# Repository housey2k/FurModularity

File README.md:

# FurModularity
Smart watch/audio mixer/module hub/game console/whatever
The FurModularity is a """watch""" meant "For Modularity", it's based on a ESP32-S3 as it's brain

It has 5 input/output connectors for external modules, these modules can be anything, be it a flashlight, a laser pointer, SD card, a second screen, or anything you can imagine, these modules interface with the main board through a SPI bus, a microcontroller inside the module card must interface between the actual module device and the ESP32, this allows more flexibility since a driver on the watch and custom code on the slave microcontroller allows for way more customization than directly interfacing the SPI bus with the module device, it would result in a way more limited module selection, or require you to manually select what kind of module is connected on the user inteface, which would ruin the hotplugging since you'd need to open settings every time you connect something new.

It also has a two input and two output audio mixer, via software you can route inputs 1, 2 or both to outputs 1, 2 or both, the routing is done by two 74VHC4066M Analog Switch ICs, one for each input channel, and you can also change the input volumes, that is done by two MCP4261 ICs, one for each channel too.

I originally built this project as a curious kid exploring CAD software, and I always liked electronics, I wanted to create my own stuff, but I never had the money for it. Now with more experience I restarted this project from scratch hoping to get funds for it.

This is how the PCB looks like, the back side has no components, thus simplifying assembly:

This is how the case looks like:

And finally, here is the schematics:
This is the power circuit, it handles battery discharging, PowerPath, and generating 5V and 3.3V rails

This is the digital circuit, it shows connections from the MCU to other components in the board

This is the audio circuit, it handles audio routing and volume control, everything is controlled by the MCU

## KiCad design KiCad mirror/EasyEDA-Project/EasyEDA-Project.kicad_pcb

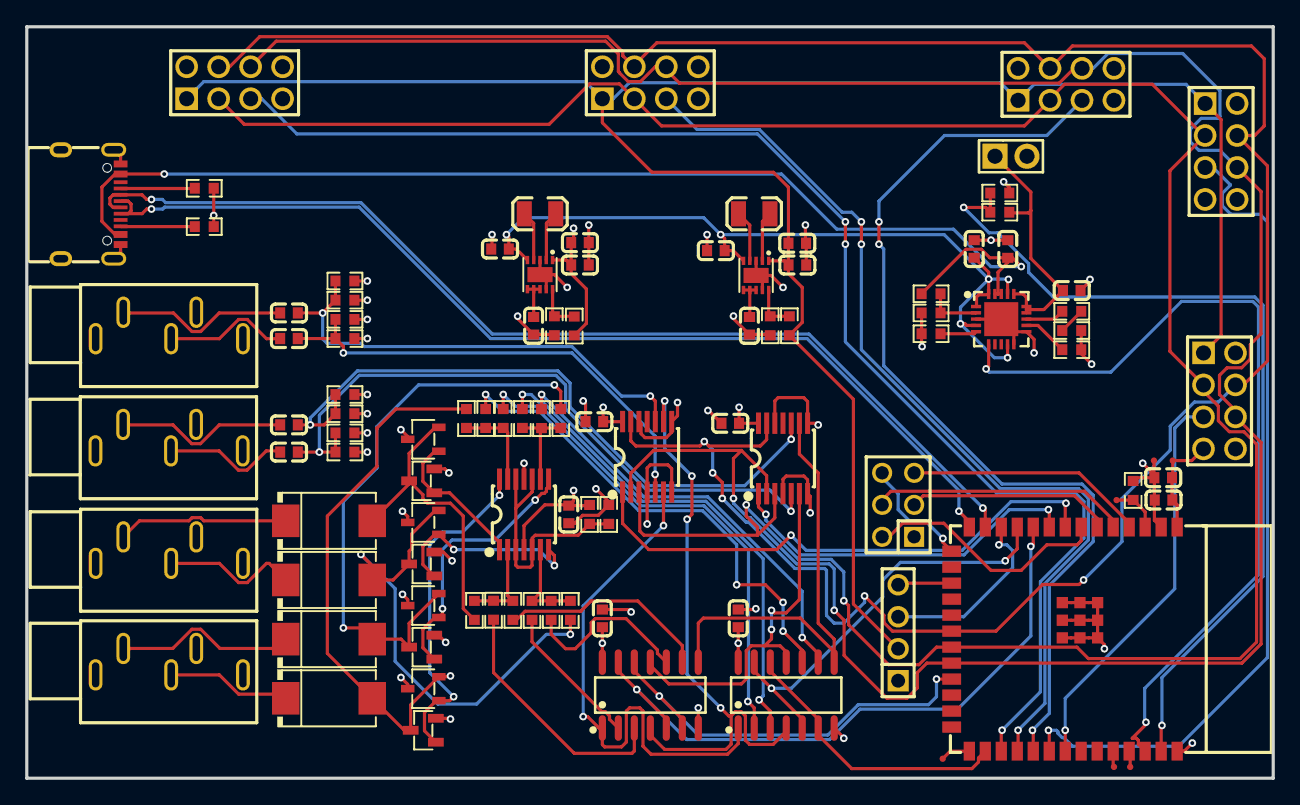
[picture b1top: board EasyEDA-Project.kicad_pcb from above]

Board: 4 copper layers, 99.0 x 59.7 mm, 101 parts (0 on the bottom side), 87 nets.

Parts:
C1, C2, C3, C4, C5, C6, C7, C8, C9, C10, C11, C12, C13, C43, C44, C45, C46, C47, C54, C55, C56, C57: C0603
C48, C49, C50, C51: CAP-SMD_L7.3-W4.3-FD
CN5, CN6, CN7, CN8: AUDIO-TH_KH-PJ-325C
H1: HDR-TH_2P-P2.54-V-M
H2: HDR-TH_4P-P2.54-V-M
H3: HDR-TH_6P-P2.54-V-R2-C3-S2.54_A2541WV-2X3P
H4, H5, H6, H7, H8: HDR-TH_8P-P2.54-V-R2-C4-S2.54_A2541WV-2X4P
L1, L2: L1207
Q1, Q3, Q5, Q7: SOT-23-3_L2.9-W1.6-P1.90-LS2.8-BR
Q2, Q4, Q6, Q8: SOT-23-3_L2.9-W1.3-P1.90-LS2.4-BR
R1, R2, R3, R4, R5, R7, R8, R9, R10, R11, R12, R14, R15, R23, R24, R25, R26, R27, R28, R29, R30, R31, R32, R33, R34, R39, R40, R41, R42, R43, R44, R45, R46, R49, R50, R51, R52: R0603
TP1, TP2, TP3, TP4, TP5, TP6: Test-Point-0.5mm
U1: QFN-20_L4.0-W4.0-P0.50-BL-EP2.7
U2, U3: SON-10_L2.5-W2.5-P0.50-TL-EP
U4: WIFIM-SMD_ESP32-S3-WROOM-1-N8
U6, U7, U8: TSSOP-14_L5.0-W4.4-P0.65-LS6.4-BL
U10, U12: SOIC-14_L8.7-W3.9-P1.27-LS6.0-BL
USB1: USB-C-SMD_TYPE-C-6PIN-2MD-073

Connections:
3V3: C6.1, C7.1, C12.1, C13.1, C43.2, C44.2, C45.2, C46.1, C47.1, H4.8, H5.8, H6.8, H7.8, H8.8, Q1.3, Q3.3, Q5.3, Q7.3, R8.2, R12.2, R39.2, R41.2, R43.2, R45.2, R51.2, TP5.1, U2.1, U4.2, U6.14, U7.14, U8.4, U10.14, U12.14
5V: C10.1, C11.1, H2.2, H4.1, H5.1, H6.1, H7.1, H8.1, R10.2, U3.1
$1N480: R1.2, USB1.4
$1N506: R2.2, USB1.10
$1N1632: R3.1, R4.2, U1.2
$1N1764: R5.2, U1.5
$1N1839: R15.2, U1.13
$1N1881: R7.2, U1.12
$1N2370: C5.1, U2.6, U2.7, U2.8
$1N2432: L1.2, U2.2
$1N2438: L1.1, U2.4
$1N2461: R8.1, R9.2, U2.10
$1N3033: R10.1, R11.2, U3.10
$1N3038: L2.2, U3.2
$1N3051: C9.1, U3.6, U3.7, U3.8
$1N3063: L2.1, U3.4
$1N4175: R14.2, R15.1
$2N491: TP2.1, U4.27
$2N495: R12.1, TP1.1, U4.3
$2N518: TP3.1, U4.37
$2N539: TP4.1, U4.36
$3N1138: R23.1, R33.2, R34.2, U8.2
$3N1139: R24.1, R25.2, R26.2, U8.6
$3N1144: R27.2, R28.2, R29.1, U8.13
$3N1145: R30.1, R31.2, R32.2, U8.9
$3N1256: Q5.1, Q6.1, U8.8
$3N2308: Q1.1, Q2.1, U8.1
$3N2351: Q3.1, Q4.1, U8.7
$3N2603: Q7.1, Q8.1, U8.14
CLK: H4.6, H5.6, H6.6, H7.6, H8.6, U4.22, U6.2, U7.2
CS1: H4.5, U4.29
CS2: H5.5, U4.30
CS3: H6.5, U4.31
CS4: H7.5, U4.32
CS5: H8.5, U4.33
CTRL_IN1_OUT1: U4.10, U10.5, U10.13
CTRL_IN1_OUT2: U4.11, U12.5, U12.13
CTRL_IN2_OUT1: U4.23, U10.6, U10.12
CTRL_IN2_OUT2: U4.28, U12.6, U12.12
DOWN: H3.4, U4.5
ENTER: H3.6, U4.15
GND: C1.1, C2.2, C3.2, C4.2, C5.2, C6.2, C7.2, C8.2, C9.2, C10.2, C11.2, C12.2, C13.2, C43.1, C44.1, C45.1, C46.2, C47.2, CN5.1, CN6.1, CN7.1, CN8.1, H1.2, H2.1, H3.1, H4.2, H4.7, H5.2, H5.7, H6.2, H6.7, H7.2, H7.7, H8.2, H8.7, Q2.2, Q4.2, Q6.2, Q8.2, R1.1, R2.1, R4.1, R5.1, R7.1, R9.1, R11.1, R14.1, R40.1, R42.1, R44.1, R46.1, R50.1, R52.1, TP6.1, U1.3, U1.10, U1.11, U1.21, U2.3, U2.9, U2.11, U3.3, U3.9, U3.11, U4.1, U4.40, U4.41, U6.4, U6.7, U6.8, U6.12, U7.4, U7.7, U7.8, U7.12, U8.11, U10.7, U12.7, USB1.1, USB1.12, USB1.13, USB1.14
IJACK1_L: C55.2, CN5.5
IJACK1_R: C54.2, CN5.2
IJACK2_L: C57.2, CN6.5
IJACK2_R: C56.2, CN6.2
IN1_L: C55.1, R41.1, R42.2, U6.10
IN1_L_SW1: R33.1, U10.3
IN1_L_SW2: R32.1, U12.3
IN1_POTOUT_L: U6.9, U10.4, U12.4
IN1_POTOUT_R: U6.6, U10.1, U12.1
IN1_R: C54.1, R39.1, R40.2, U6.5
IN1_R_SW1: R25.1, U10.2
IN1_R_SW2: R28.1, U12.2
IN2_L: C57.1, R45.1, R46.2, U7.10
IN2_L_SW1: R34.1, U10.9
IN2_L_SW2: R31.1, U12.9
IN2_POTOUT_L: U7.9, U10.8, U12.8
IN2_POTOUT_R: U7.6, U10.11, U12.11
IN2_R: C56.1, R43.1, R44.2, U7.5
IN2_R_SW1: R26.1, U10.10
IN2_R_SW2: R27.1, U12.10
LEFT: H3.2, U4.7
MISO: H4.4, H5.4, H6.4, H7.4, H8.4, U4.20, U6.13, U7.13
MOSI: H4.3, H5.3, H6.3, H7.3, H8.3, U4.21, U6.3, U7.3
OJACK1_L: C48.1, CN7.5
OJACK1_R: C49.1, CN7.2
OJACK2_L: C51.1, CN8.5
OJACK2_R: C50.1, CN8.2
OUT1_L: C48.2, Q1.2, Q2.3, R23.2
OUT1_R: C49.2, Q3.2, Q4.3, R24.2
OUT2_L: C51.2, Q5.2, Q6.3, R30.2
OUT2_R: C50.2, Q7.2, Q8.3, R29.2
P1_CS: U4.8, U6.1
P2_CS: U4.9, U7.1
REF_1V65: R51.1, R52.2, U8.3, U8.5, U8.10, U8.12
RIGHT: H3.3, U4.6
SCL: H2.4, U4.17
SDA: H2.3, U4.12
UP: H3.5, U4.4
USB_DM: U4.13, USB1.5, USB1.7
USB_DP: U4.14, USB1.6, USB1.8
USB_SENSE: U1.6, U4.38
VBAT: C3.1, H1.1, R49.2, U1.14, U1.15, U1.16
VBAT_SENSE: R49.1, R50.2, U4.39
VBUS: C1.2, R3.2, U1.18, U1.19, USB1.2, USB1.11
VSYS: C2.1, C4.1, C8.1, U1.1, U1.4, U1.9, U1.17, U1.20, U2.5, U3.5

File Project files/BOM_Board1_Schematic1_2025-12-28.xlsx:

No. | Quantity | Comment | Designator | Footprint | Value | Manufacturer Part | Manufacturer | Supplier Part | Supplier | LCSC Price | LCSC Stock | JLCPCB Price | Pin Count | Primary Category | Secondary Category | JLCPCB Stock
1 | 13 | 10uF | C1,C4,C6,C7,C8,C10,C11,C46,C47,C54,C55,C56,C57 | C0603 | 10uF | C0603B106M007T | IHHEC(禾伸堂) | C7094065 | LCSC |  |  | 0.0012 | 2 |  |  | 3674
2 | 2 | 4.7uF | C2,C3 | C0603 | 4.7uF | CL10A475KP8NNNC | SAMSUNG(三星) | C1705 | LCSC |  |  | 0.0008 | 2 |  |  | 3827044
3 | 7 | 100nF | C5,C9,C12,C13,C43,C44,C45 | C0603 | 100nF | CC0603KRX7R9BB104 | YAGEO(国巨) | C14663 | LCSC |  |  | 0.0004 | 2 |  |  | 68279201
4 | 4 | 470uF | C48,C49,C50,C51 | CAP-SMD_L7.3-W4.3-FD | 470uF | CA45-D-6.3V-470UF-K | CEC(振华新云) | C2841148 | LCSC |  |  | 0.1055 | 2 |  |  | 371
5 | 4 | KH-PJ-325C | CN5,CN6,CN7,CN8 | AUDIO-TH_KH-PJ-325C |  | KH-PJ-325C | kinghelm(金航标) | C5123138 | LCSC |  |  | 0.0263 | 5 | Connectors | Audio Connectors | 425
6 | 1 | PZ254V-11-02P | H1 | HDR-TH_2P-P2.54-V-M |  | PZ254V-11-02P | XFCN(兴飞) | C492401 | LCSC |  |  | 0.0018 | 2 | Connectors | Pin Headers | 576750
7 | 1 | PZ254V-11-04P | H2 | HDR-TH_4P-P2.54-V-M |  | PZ254V-11-04P | XFCN(兴飞) | C2691448 | LCSC |  |  | 0.0031 | 4 | Connectors | Pin Headers | 594475
8 | 1 | 2.54-2*3 | H3 | HDR-TH_6P-P2.54-V-R2-C3-S2.54_A2541WV-2X3P |  | 2.54-2*3 | ZHOURI(洲日) | C5116479 | LCSC |  |  | 0.0081 | 6 |  |  | 16497
9 | 5 | A2541WV-2x4P | H4,H5,H6,H7,H8 | HDR-TH_8P-P2.54-V-R2-C4-S2.54_A2541WV-2X4P |  | A2541WV-2x4P | CJT(长江连接器) | C225519 | LCSC |  |  | 0.0179 | 8 | Connectors | Pin Headers | 9182
10 | 2 | 1.5uH | L1,L2 | L1207 | 1.5uH | LB3218T1R5M | TAIYO YUDEN(太诱) | C223380 | LCSC |  |  | 0.0065 | 2 |  |  | 0
11 | 4 | MMBT2222A | Q1,Q3,Q5,Q7 | SOT-23-3_L2.9-W1.6-P1.90-LS2.8-BR |  | MMBT2222A | TDSEMIC(拓电半导体) | C42441802 | LCSC |  |  |  | 3 | Transistors/Thyristors | Bipolar (BJT) | 0
12 | 4 | MMBT2907A | Q2,Q4,Q6,Q8 | SOT-23-3_L2.9-W1.3-P1.90-LS2.4-BR |  | MMBT2907A | R+O(宏嘉诚) | C7420352 | LCSC |  |  | 0.002 | 3 | Transistors/Thyristors | Bipolar (BJT) | 65573
13 | 2 | 5.1kΩ | R1,R2 | R0603 | 5.1kΩ | HoAR0603-1/10W-5.1KR-0.1%-TCR25 | Milliohm(毫欧) | C5123587 | LCSC |  |  | 0.0072 | 2 |  |  | 974
14 | 1 | 330kΩ | R3 | R0603 | 330kΩ | HPCR0603F330KK9 | RESI(开步睿思) | C365145 | LCSC |  |  | 0.0001 | 2 |  |  | 0
15 | 1 | 110kΩ | R4 | R0603 | 110kΩ | PTFR0603B110KN9 | RESI(开步睿思) | C2692888 | LCSC |  |  | 0.0255 | 2 |  |  | 3518
16 | 10 | 10kΩ | R5,R12,R39,R40,R41,R42,R43,R44,R45,R46 | R0603 | 10kΩ | SCR0603J10K | VO(翔胜) | C3017715 | LCSC |  |  | 0.0002 | 2 |  |  | 104777
17 | 1 | 100kΩ | R7 | R0603 | 100kΩ | SCR0603F100K | VO(翔胜) | C3016388 | LCSC |  |  | 0.0002 | 2 |  |  | 13910
18 | 1 | 1.13MΩ | R8 | R0603 | 1.13MΩ | RTT031134FTP | RALEC(旺诠) | C166907 | LCSC |  |  | 0.0003 | 2 |  |  | 2966
19 | 2 | 200kΩ | R9,R11 | R0603 | 200kΩ | SCR0603F200K | VO(翔胜) | C5140262 | LCSC |  |  | 0.0002 | 2 |  |  | 14305
20 | 1 | 1.8MΩ | R10 | R0603 | 1.8MΩ | FRC0603J185TS | FOJAN(富捷) | C2930026 | LCSC |  |  | 0.0002 | 2 |  |  | 52884
21 | 18 | 1kΩ | R14,R15,R23,R24,R25,R26,R27,R28,R29,R30,R31,R32,R33,R34,R49,R50,R51,R52 | R0603 | 1kΩ | 0603WAF1001T5E | UNI-ROYAL(厚声) | C21190 | LCSC |  |  | 0.0002 | 2 |  |  | 46024417
22 | 6 | Test-Point | TP1,TP2,TP3,TP4,TP5,TP6 | Test-Point-0.5mm |  |  |  |  |  | 26.0869 |  |  | 1
23 | 1 | MCP73871-2CAI/ML | U1 | QFN-20_L4.0-W4.0-P0.50-BL-EP2.7 |  | MCP73871-2CAI/ML | MICROCHIP(美国微芯) | C185603 | LCSC |  |  | 0.575 | 21 | Power Management (PMIC) | Battery Management | 91
24 | 2 | TPS63030DSKTG4 | U2,U3 | SON-10_L2.5-W2.5-P0.50-TL-EP |  | TPS63030DSKTG4 | TI(德州仪器) | C2072808 | LCSC |  |  | 0.2416 | 11 | Power Management (PMIC) | DC-DC Converters | 0
25 | 1 | ESP32-S3-WROOM-1-N4 | U4 | WIFIM-SMD_ESP32-S3-WROOM-1-N8 |  | ESP32-S3-WROOM-1-N4 | ESPRESSIF(乐鑫) | C2913197 | LCSC |  |  | 0.6165 | 41 | IoT/Communication Modules | WiFi Modules | 1248
26 | 2 | MCP4261-103E/ST | U6,U7 | TSSOP-14_L5.0-W4.4-P0.65-LS6.4-BL |  | MCP4261-103E/ST | MICROCHIP(美国微芯) | C185580 | LCSC |  |  | 0.2885 | 14 |  |  | 0
27 | 1 | LMV324IPWRE4 | U8 | TSSOP-14_L5.0-W4.4-P0.65-LS6.4-BL |  | LMV324IPWRE4 | TI(德州仪器) | C4366614 | LCSC |  |  | 0.0426 | 14 |  |  | 0
28 | 2 | 74VHC4066M | U10,U12 | SOIC-14_L8.7-W3.9-P1.27-LS6.0-BL |  | 74VHC4066M | onsemi(安森美) | C3656918 | LCSC |  |  | 0.0364 | 14 |  |  | 0
29 | 1 | TYPE-C 16PIN 2MD(073) | USB1 | USB-C-SMD_TYPE-C-6PIN-2MD-073 |  | TYPE-C 16PIN 2MD(073) | SHOU HAN(首韩) | C2765186 | LCSC |  |  | 0.0089 | 14 | Connectors | USB Connectors | 347871

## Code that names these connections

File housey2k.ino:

#include <Wire.h>
#include <SPI.h>
#include <String.h>
#include <LiquidCrystal_I2C.h>
#include <MCP4261.h>

// SPI Bus BEGIN
#define MOD_CS1 36
#define MOD_CS2 37
#define MOD_CS3 38
#define MOD_CS4 39
#define MOD_CS5 40

#define P1_CS 15
#define P2_CS 16
// SPI Bus END

// GPIO BEGIN
#define ENTER 3
#define UP 4
#define DOWN 5
#define RIGHT 6
#define LEFT 7

#define CTRL_IN1_OUT1 17
#define CTRL_IN1_OUT2 18
#define CTRL_IN2_OUT1 21
#define CTRL_IN2_OUT2 35
// GPIO END

// BUS BEGIN
#define LCD_ADDR 0x27
#define SDA 8
#define SCL 9

#define MISO 12
#define MOSI 13
#define SCK 14
// BUS END

LiquidCrystal_I2C lcd(LCD_ADDR, 20, 4);
MCP4261 pot1(P1_CS, 255, &SPI);
MCP4261 pot2(P2_CS, 255, &SPI);

void I2C_Scan(void)
{
  byte error, address;
  int nDevices;

  Serial.println("Scanning...");
  nDevices = 0;
  for(address = 1; address < 127; address++ ) {
    Wire.beginTransmission(address);
    error = Wire.endTransmission();
    if (error == 0) {
      Serial.print("I2C device found at address 0x");
      if (address<16) {
        Serial.print("0");
      }
      Serial.println(address, HEX);
      nDevices++;
    }
    else if (error==4) {
      Serial.print("Unknow error at address 0x");
      if (address<16) {
        Serial.print("0");
      }
      Serial.println(address, HEX);
    }    
  }
  if (nDevices == 0) {
    Serial.println("No I2C devices found\n");
  }
  else {
    Serial.println("done\n");
  }
}

void spiSendBuffer(const uint8_t *buf, size_t len) {
  for (size_t i = 0; i < len; i++) {
    SPI.transfer(buf[i]);
  }
}

void spiReadBuffer(uint8_t *buf, size_t len) {
  for (size_t i = 0; i < len; i++) {
    buf[i] = SPI.transfer(0x00);
  }
}

String Module_scan() {
  static const uint8_t detectCmd[] = { 'D','E','T','E','C','T' };
  uint8_t reply[4];

  const uint8_t csList[] = {
    MOD_CS1,
    MOD_CS2,
    MOD_CS3,
    MOD_CS4,
    MOD_CS5
  };

  String output;
  output.reserve(sizeof(csList));

  SPI.beginTransaction(SPISettings(
    500000,
    MSBFIRST,
    SPI_MODE0
  ));

  for (size_t i = 0; i < sizeof(csList); i++) {
    digitalWrite(csList[i], LOW);
    delayMicroseconds(5);

    spiSendBuffer(detectCmd, sizeof(detectCmd));
    delayMicroseconds(20);          // give slave time
    spiReadBuffer(reply, sizeof(reply));

    digitalWrite(csList[i], HIGH);

    output += (memcmp(reply, "HERE", 4) == 0) ? '1' : '0';
    delay(5);
  }

  SPI.endTransaction();
  return output;
}

void print(String msg, bool printToLCD_Y3) {
  Serial.println(msg);
  if (!printToLCD_Y3) { return; }
  lcd.setCursor(0, 3);
  lcd.print("                    ");
  lcd.setCursor(0, 3);
  lcd.print(msg);
}

bool RW_MCP4261(MCP4261 pot, int wiper) {
  bool success = false;
  pot.setValue(wiper, 123);
  if (pot.getValueDevice(wiper) == 123) {
    success = true;
  }
  return success;
}

void halt() {
  while (true) {}
}

String Connected_modules;

bool RenderedMenu;
bool RenderedArrow;

int ArrowX;
int ArrowY;
int PrevArrowX;
int PrevArrowY;

String CurrMenu;

bool UpPressed;
bool DownPressed;
bool RightPressed;
bool LeftPressed;

int ArrowRawX;
int ArrowRawY;

void setup(void) {
  Serial.begin(115200);
  print("HouseY2K OS", false);

  Wire.begin(SDA, SCL);
  print("Initialized I2C bus", false);

  I2C_Scan();
  print("Hardcoded LCD addr: #define LCD_ADDR ", false);
  Serial.println(LCD_ADDR);

  lcd.init();
  print("LCD init() done", true);
  lcd.backlight();
  print("LCD backlight() done", true);

  lcd.print("FurModularity DEV FW");
  lcd.setCursor(0, 1);
  lcd.print("HouseY2K OS V0.1");
  lcd.setCursor(0, 2);
  lcd.print("Booting...");
  print("Initializing SPI...", true);
  SPI.begin(SCK, MISO, MOSI, -1);
  delay(100);

  print("Initializing pins...", true);
  pinMode(MOD_CS1, OUTPUT);
  pinMode(MOD_CS2, OUTPUT);
  pinMode(MOD_CS3, OUTPUT);
  pinMode(MOD_CS4, OUTPUT);
  pinMode(MOD_CS5, OUTPUT);

  pinMode(ENTER, INPUT_PULLUP);
  pinMode(UP, INPUT_PULLUP);
  pinMode(DOWN, INPUT_PULLUP);
  pinMode(RIGHT, INPUT_PULLUP);
  pinMode(LEFT, INPUT_PULLUP);

  pinMode(CTRL_IN1_OUT1, INPUT_PULLUP);
  pinMode(CTRL_IN1_OUT2, INPUT_PULLUP);
  pinMode(CTRL_IN2_OUT1, INPUT_PULLUP);
  pinMode(CTRL_IN2_OUT2, INPUT_PULLUP);

  delay(100);

  print("POST MCP4261", true);
  delay(100);

  print("INIT MCP4261", true);
  pot1.begin();
  pot2.begin();
  delay(100);

  print("RW MCP4261 IC1 W0", true);
  if (RW_MCP4261(pot1, 0)) {
    print("OK", true);
  } else {
    print("ERROR IC1 W0", true);
    halt();
  }

  delay(100);

  print("RW MCP4261 IC1 W1", true);
  if (RW_MCP4261(pot1, 1)) {
    print("OK", true);
  } else {
    print("ERROR IC1 W1", true);
    halt();
  }

  delay(100);

  print("RW MCP4261 IC2 W0", true);
  if (RW_MCP4261(pot2, 0)) {
    print("OK", true);
  } else {
    print("ERROR IC2 W0", true);
    halt();
  }

  delay(100);

  print("RW MCP4261 IC2 W1", true);
  if (RW_MCP4261(pot2, 1)) {
    print("OK", true);
  } else {
    print("ERROR IC2 W1", true);
    halt();
  }

  delay(100);
  

  print("Scanning modules...", true);
  Connected_modules = Module_scan();

  print("mdet:" + Connected_modules, true);

  delay(1000);
  print("Initializing vars", true);

  RenderedMenu = false;
  CurrMenu = "NULL";

  RenderedArrow = false;
  ArrowX = 0;
  ArrowY = 0;

  PrevArrowX = 0;
  PrevArrowY = 0;

  ArrowRawX = 0;
  ArrowRawY = 0;

  UpPressed = false;
  DownPressed = false;
  RightPressed = false;
  UpPressed = false;
  delay(100);
  print("BootOK LoadOS", true);
}


void RenderMainMenu(String Mods) {
  lcd.clear();
  lcd.setCursor(0, 0);

  lcd.print(" MODS USB ");
  lcd.setCursor(0, 1);
  lcd.print("MIXER PWR");
  lcd.setCursor(0, 2);
  lcd.print(" WiFi BATT");
  lcd.setCursor(0, 2);
  lcd.print(" BLE ");
}

void RenderArrow(int X, int Y) {
  RenderedArrow = true;
  lcd.setCursor(PrevArrowX, PrevArrowY);
  lcd.print(" ");
  lcd.setCursor(X, Y);
  lcd.print(">");
  PrevArrowX = X;
  PrevArrowY = Y;
}

// Gets the position to write the arrow on screen, rawpos is the numerical value based on the increments or decrements from left/right buttons
int GetArrowXPos(int rawPos) {
  if (CurrMenu == "MAIN") {
    if (rawPos == 0) {
      return 0;
    } else if (rawPos == 1) {
      return 5;
    } else if (rawPos == 2) {
      return 9;
    }
  }
  return 0;
}

// Gets the position to write the arrow on screen, rawpos is the numerical value based on the increments or decrements from up/down buttons
int GetArrowYPos(int rawPos) {
  /*if (CurrMenu == "MAIN") {
    if (rawPos == 0) {
      return 0;
    } else if (rawPos == 1) {
      return 1;
    } else if (rawPos == 2) {
      return 2;
    }
  }*/
  return rawPos;
}

void loop(void) {

  if (!digitalRead(UP) && !UpPressed) {
    UpPressed = true;
    RenderedArrow = false;
    ArrowRawY++;
  } else if (digitalRead(UP)) {
    UpPressed = false;
  }

  if (!digitalRead(DOWN) && !DownPressed) {
    DownPressed = true;
    RenderedArrow = false;
    ArrowRawY--;
  } else if (digitalRead(DOWN)) {
    DownPressed = false;
  }

  if (!digitalRead(RIGHT) && !RightPressed) {
    RightPressed = true;
    RenderedArrow = false;
    ArrowRawX++;
  } else if (digitalRead(RIGHT)) {
    RightPressed = false;
  }

  if (!digitalRead(LEFT) && !LeftPressed) {
    LeftPressed = true;
    RenderedArrow = false;
    ArrowRawX--;
  } else if (digitalRead(LEFT)) {
    LeftPressed = false;
  }

  if (CurrMenu == "NULL")
  {
    CurrMenu = "MAIN";
    RenderedMenu = true;
    RenderMainMenu(Connected_modules);
  }

  if (!RenderedArrow) {
    RenderArrow(GetArrowXPos(ArrowRawX), GetArrowYPos(ArrowRawY));
  }
}

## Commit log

2025-12-27 PCB_final
2025-12-27 Rename Captura de tela 2025-12-27 185347.png to PCB_Final
2025-12-27 Rename ProPrj_FurModularity 2_2025-12-27.epro to EasyEDA_proj
2025-12-27 Rename EasyEDA_proj to EasyEDA_proj.epro
2025-12-27 Rename PCB_Final to PCB_Final.jpg
2025-12-27 Enhance README with detailed project description
    Expanded the description of the FurModularity project, detailing its features and capabilities.
2025-12-28 firmware wip
2025-12-28 Add comments
2025-12-28 Organization
2026-01-02 Enhance README with project background and images
    Added personal project background and images to README.
2026-01-02 move img
2026-01-02 aaaaaaaaaaaa
2026-01-08 Revise README with new images and circuit schematics
    Updated images and added schematics for power, digital, and audio circuits.
2026-01-08 Update BOM, sch and readme for review
2026-01-08 Added missing PCB image
2026-01-08 Added spacing
2026-01-23 Add KiCad mirror
2026-01-24 Add 3D files
2026-01-31 Commit I forgot
2026-01-31 add more case img
    aaaaaaaaahhhhhhhhhhhhhhh
2026-02-14 Rounded corners on 3D
    Rounded corners on 3D
